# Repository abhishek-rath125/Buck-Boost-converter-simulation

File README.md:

# Single-Stage Buck / Boost Demonstrator (555-timer PWM & KiCad PCB)

**Author:** Abhishek Rathour — B.Tech, Electrical & Electronics Engineering, NIT Goa

A complete power electronics project demonstrating **buck-mode (step-down) and boost-mode (step-up) behaviour from a single power-stage topology**, featuring both **LTspice simulation suites** and a physical **KiCad 10 hardware design & 2-layer PCB layout**.

---

## 📸 Hardware Previews

| Assembled 3D Board Render | KiCad 2-Layer PCB Layout |
|:---:|:---:|
|  |  |
| *3D view showing electrolytic cap bank, TO-220 MOSFET heatsink, NE555P, trimmer pot & inductors* | *2-layer routed board (`buckboostv1.kicad_pcb`)* |

### KiCad Schematic Diagram

*Complete hardware schematic (`hardware/buckboostv1.kicad_sch`) with NE555P astable PWM generator, potentiometer duty-cycle steering, and dual-inductor SEPIC power stage.*

---

## ⚡ What this is

A unified simulation and hardware project demonstrating how a single power stage behaves as either a **buck converter** (output below $V_{in}$) or a **boost converter** (output above $V_{in}$), purely by controlling the PWM switch duty cycle:

- **Duty cycle $D < 50\%$** $\longrightarrow$ Buck mode (step-down magnitude).
- **Duty cycle $D > 50\%$** $\longrightarrow$ Boost mode (step-up magnitude).

The repository documents the complete engineering trail:
1. **LTspice Simulation Trail:** Diagnosing inverting-topology issues, migrating to a two-inductor SEPIC stage, solving ripple current via switching frequency vs. duty-cycle moderation, and isolating the 555 supply rail.
2. **KiCad Hardware Implementation (`buckboostv1`):** Translating the simulation into a physical, manufacture-ready 2-layer PCB with a single potentiometer (`RV1`) for continuous, real-time duty cycle tuning on the lab bench.

---

## 🗂️ Repo Structure

```
├── hardware/
│   ├── buckboostv1.kicad_pro        # KiCad 10 project definition
│   ├── buckboostv1.kicad_sch        # Hardware schematic
│   ├── buckboostv1.kicad_pcb        # 2-layer routed PCB layout
│   ├── schematic.pdf                # High-res vector PDF export
│   ├── buckboostv1.svg              # Scalable vector graphics export
│   ├── bom.csv                      # Full Bill of Materials
│   ├── README.md                    # Hardware & PCB fabrication guide
│   └── gerbers/                     # Production Gerbers & NC drill files (JLCPCB/PCBWay)
├── ltspice/
│   ├── v1_sepic_fast_switching/     # Two-inductor power stage, 131 kHz switching
│   ├── draft1_555_vcc_isolation_test/ # Standalone 12V 555 testbench
│   └── v3_final/                    # Converter with dedicated 12V rail, 13.1 kHz
├── docs/
│   ├── 01-topology-and-goal.md      # Dual-mode operation & diode-steered 555 astable
│   ├── 02-v1-sepic-fast-switching.md
│   ├── 03-draft1-vcc-isolation-test.md
│   ├── 04-v3-final-fixes.md
│   ├── 05-hardware-kicad-pcb.md     # Detailed hardware & PCB design notes
│   ├── hardware/                    # Board renders and layout screenshots
│   └── v3_simulation_result.png     # LTspice waveform verification
├── CHANGELOG.md                     # Revision history
├── LICENSE                          # MIT License
└── README.md
```

---

## 🛠️ Hardware & PCB Design Details

### Continuous Duty Cycle Tuning via Potentiometer `RV1`
In physical hardware, fixed resistors are replaced by a **10kΩ vertical trimmer potentiometer (`RV1`)** coupled with antiparallel steering diodes `D1` and `D2`:
- Turning `RV1` clockwise increases charging resistance $\rightarrow$ **Duty cycle $D > 50\%$ (Boost)**.
- Turning `RV1` counter-clockwise increases discharge resistance $\rightarrow$ **Duty cycle $D < 50\%$ (Buck)**.
- A single knob controls real-time continuous transitions from step-down to step-up.

### Key Hardware Components
| Reference | Part | Package | Role |
|---|---|---|---|
| **U1** | NE555P | DIP-8 | High-precision PWM astable oscillator |
| **Q1** | IRF3205 | TO-220 / TO-218 | 55V, 110A, 8mΩ N-Channel power MOSFET |
| **RV1** | Potentiometer | ACP CA9-V10 | Real-time duty-cycle adjustment |
| **D1, D2** | 1N4148 / DO-35 | Axial | Independent charge/discharge steering diodes |
| **D3** | BAT54C / Schottky | TO-126-3 | Ultra-fast freewheeling diode |
| **L2, L3** | Power Chokes | Fastron MECC Axial | Energy storage dual inductors |
| **C2-C5** | Radial Electrolytic | D10mm, P5mm | Low-ESR AC coupling, filter & timing caps |
| **J1** | 2-Pin Terminal | JWT A3963 | DC power input connector |

Fabrication Gerbers and drill files are located in [`hardware/gerbers/`](hardware/gerbers/). See [`hardware/README.md`](hardware/README.md) for manufacturing guidelines.

---

## 📊 Simulation Summary (LTspice)

| Parameter | v1 | Draft1 | v3 (Final) |
|---|---|---|---|
| **Power stage** | SEPIC-style, 2 inductors | *(none — timer only)* | SEPIC-style, 2 inductors |
| **Switching frequency** | 1nF $\rightarrow$ **~131 kHz** | 10nF $\rightarrow$ ~9.3 kHz | 10nF $\rightarrow$ **~13.1 kHz** |
| **Duty cycle (2 channels)** | 27.3% / **81.8%** | 29.5% (single channel) | **39.1% / 63.6%** |
| **Inductor ripple current** | ~0.5 A / ~1.5 A | n/a | ~0.7 A / ~1.2 A |
| **555 Vcc** | Shared 24V rail ⚠️ | **Dedicated 12V** ✅ | **Dedicated 12V** ✅ |
| **Coupling-cap damping** | none | n/a | 22 Ω (`R11`/`R12`) |
| **Output-cap ESR** | none | n/a | modeled (`Rser = 0.1Ω`) |

### Verification Waveforms (v3)

With input $V_{ref} = 24\,\text{V}$:
- **Buck Channel (`U1`, $D = 39.1\%$):** Output settles at **$13.50\,\text{V}$** (step-down confirmed).
- **Boost Channel (`U2`, $D = 63.6\%$):** Output settles at **$29.43\,\text{V}$** (step-up confirmed).

---

## 💻 How to Open the Design Files

- **KiCad Design Files:** Open [`hardware/buckboostv1.kicad_pro`](hardware/buckboostv1.kicad_pro) in **KiCad 10** (or 8 / 9). All footprints, schematic symbols, and 3D models use standard KiCad libraries.
- **LTspice Simulations:** Open any `.asc` file in [`ltspice/`](ltspice/) using free LTspice (Windows, macOS, or Wine on Linux). Built-in generic models are used throughout.

---

## 📜 License

MIT License — see [LICENSE](LICENSE).

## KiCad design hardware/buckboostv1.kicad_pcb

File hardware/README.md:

# Hardware & PCB Implementation (KiCad 10)

This directory contains the complete hardware design, schematic, 2-layer PCB layout, Bill of Materials (BOM), and manufacturing Gerber files for the **Single-Stage Buck / Boost Demonstrator**.

---

## 📐 Circuit Architecture

The hardware translates the dual-mode SEPIC / buck-boost topology into a physical board powered by a single supply and tuned in real time via an on-board trimmer potentiometer:

1. **Continuous Duty-Cycle PWM Generator (NE555P):**
   - Configured as an astable multivibrator with diode steering (`D1`, `D2`).
   - Single trimmer potentiometer (`RV1`) adjusts the ratio between charge resistance and discharge resistance without changing total cycle period drastically.
   - Turning `RV1` allows seamless on-the-fly transition between **Buck mode ($D < 50\%$)** and **Boost mode ($D > 50\%$)**.
   - Output pin 3 drives the gate of power MOSFET `Q1` through gate damping resistor `R2`.

2. **SEPIC Power Stage:**
   - **Switch (`Q1`):** IRF3205 N-Channel MOSFET in a TO-220/TO-218 vertical package mounted with heatsink clearance for thermal dissipation.
   - **Inductors (`L3`, `L2`):** Dual high-current inductors (input choke and output inductor) supporting energy storage in both CCM and DCM modes.
   - **Coupling Capacitor (`C3`):** High-capacitance electrolytic block blocking DC while passing switching ripple.
   - **Freewheeling Diode (`D3`):** Fast switching Schottky diode (`BAT54C` / TO-126 package) for low forward drop and minimal reverse recovery losses.
   - **Output Filter (`C4`, `R4`):** Low-ESR electrolytic capacitor bank with dummy load resistor `R4`.

---

## 📦 Bill of Materials (BOM)

| Reference | Value / Part | Package / Footprint | Description / Purpose |
|---|---|---|---|
| **U1** | NE555P | DIP-8 (`W7.62mm`) | Precision Timer IC (PWM oscillator) |
| **Q1** | IRF3205 | TO-218-3 / TO-220 Vertical | 55V, 110A, 8mΩ N-Channel Power MOSFET |
| **RV1** | R_Potentiometer | ACP CA9-V10 Vertical | Trimmer potentiometer for duty cycle tuning |
| **D1, D2** | Fast Switching Diode | DO-35 (SOD27) / Axial | Steering diodes for independent charge/discharge |
| **D3** | BAT54C / Schottky | TO-126-3 Vertical | High-speed freewheeling rectifier |
| **L2, L3** | Inductors (Power Chokes) | Axial Fastron MECC (`P7.62mm`) | Dual energy storage inductors |
| **C2** | Filter Cap | Radial D10mm, P5.0mm | 555 Pin 5 (CONT) noise decoupling |
| **C3** | Coupling Cap | Radial D10mm, P5.0mm | AC energy transfer capacitor |
| **C4** | Output Cap | Radial D10mm, P5.0mm | DC output voltage smoothing filter |
| **C5** | Timing Cap | Radial D10mm, P5.0mm | 555 astable timing capacitor |
| **R1** | Pull-up Resistor | Axial DIN0204 (`P5.08mm`) | Discharge pullup from Vcc to Pin 7 |
| **R2** | Gate Resistor | Axial DIN0204 (`P5.08mm`) | MOSFET gate damping resistor (suppresses ringing) |
| **R3** | Damping Resistor | Axial DIN0204 (`P5.08mm`) | Coupling-loop damping resistor |
| **R4** | Load Resistor | Axial DIN0204 (`P5.08mm`) | Output test load |
| **J1** | Conn_01x02_Pin | JWT A3963 2-pin (`P3.96mm`) | DC power input connector |

---

## 🗂️ File Directory

- [`buckboostv1.kicad_pro`](buckboostv1.kicad_pro) — KiCad 10 project definition file.
- [`buckboostv1.kicad_sch`](buckboostv1.kicad_sch) — Complete hierarchical schematic with netlabels and title block.
- [`buckboostv1.kicad_pcb`](buckboostv1.kicad_pcb) — 2-layer routed PCB layout with power planes.
- [`schematic.pdf`](schematic.pdf) — High-resolution vector PDF export of the schematic.
- [`buckboostv1.svg`](buckboostv1.svg) — Scalable vector graphics export of the schematic.
- [`bom.csv`](bom.csv) — Comma-separated Bill of Materials export.
- [`gerbers/`](gerbers/) — Production-ready Gerber and Excellon drill files.

---

## 🏭 PCB Fabrication Details

The files in [`gerbers/`](gerbers/) are directly compatible with standard PCB fabricators (JLCPCB, PCBWay, OSH Park):

| Extension | Layer Description | Fabricator Layer Name |
|---|---|---|
| `.gtl` | Front / Top Copper | Top Layer |
| `.gbl` | Back / Bottom Copper | Bottom Layer |
| `.gts` | Front / Top Solder Mask | Top Solder Mask |
| `.gbs` | Back / Bottom Solder Mask | Bottom Solder Mask |
| `.gto` | Front / Top Silkscreen | Top Overlay / Silkscreen |
| `.gbo` | Back / Bottom Silkscreen | Bottom Overlay / Silkscreen |
| `.gm1` | Board Outline / Edge Cuts | Mechanical 1 / Edge Cuts |
| `.drl` | Excellon NC Drill File | Plated / Non-Plated Through Holes |

### Recommended Fab Specifications:
- **Board Thickness:** 1.6 mm
- **Copper Weight:** 1 oz (35 µm) or 2 oz (for high current demonstrator runs)
- **Minimum Trace Width / Spacing:** 0.25 mm / 0.25 mm
- **Surface Finish:** HASL (with lead) or ENIG
- **Solder Mask Color:** Green / Matte Black

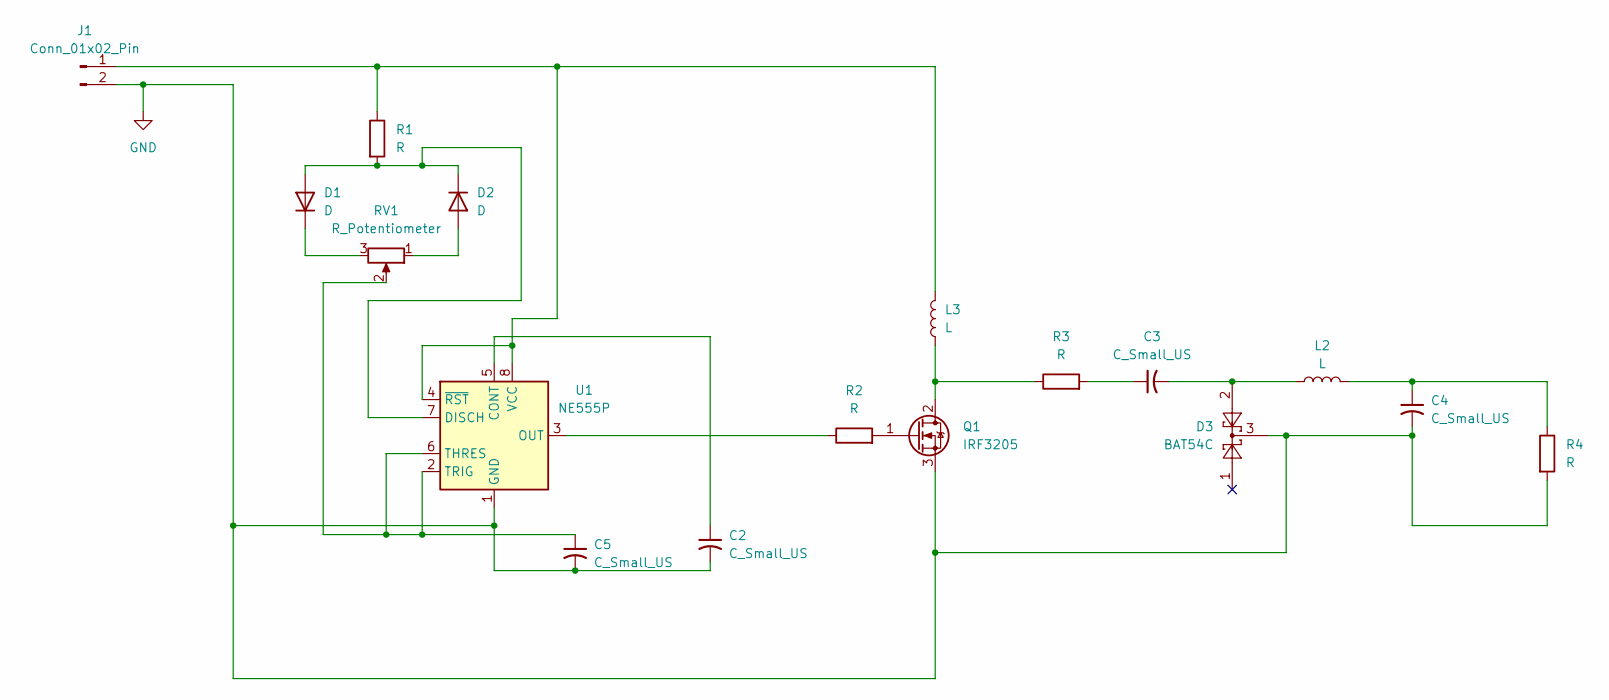
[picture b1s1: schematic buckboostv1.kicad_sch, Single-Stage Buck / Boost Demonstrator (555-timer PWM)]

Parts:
C2, C3, C4, C5: C_Small_US; CP_Radial_D10.0mm_P5.00mm
D1: D; D_DO-35_SOD27_P7.62mm_Horizontal
D2: D
D3: BAT54C; TO-126-3_Vertical
J1: Conn_01x02_Pin; JWT_A3963_1x02_P3.96mm_Vertical
L2, L3: L; L_Axial_L11.0mm_D4.5mm_P7.62mm_Vertical_Fastron_MECC
Q1: IRF3205; TO-218-3_Vertical
R1, R2, R3, R4: R; R_Axial_DIN0204_L3.6mm_D1.6mm_P5.08mm_Horizontal
RV1: R_Potentiometer; Potentiometer_ACP_CA9-V10_Vertical
U1: NE555P; DIP-8_W7.62mm

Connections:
GND: C2.2, C4.2, C5.2, D3.3, J1.2, Q1.3 (S), R4.2, U1.1 (GND)
unnamed: C3.1, R3.2
unnamed: C3.2, D3.2, L2.1
unnamed: C4.1, L2.2, R4.1
unnamed: D1.2 (A), D2.1 (K), R1.2, U1.7 (DISCH)
unnamed: D1.1 (K), RV1.3
unnamed: D2.2 (A), RV1.1
unnamed: J1.1, L3.2, R1.1, U1.4 (~RST), U1.8 (VCC)
unnamed: L3.1, Q1.2 (D), R3.1
unnamed: Q1.1 (G), R2.2
unnamed: C2.1, U1.5 (CONT)
unnamed: R2.1, U1.3 (OUT)
unnamed: C5.1, RV1.2, U1.2 (TRIG), U1.6 (THRES)

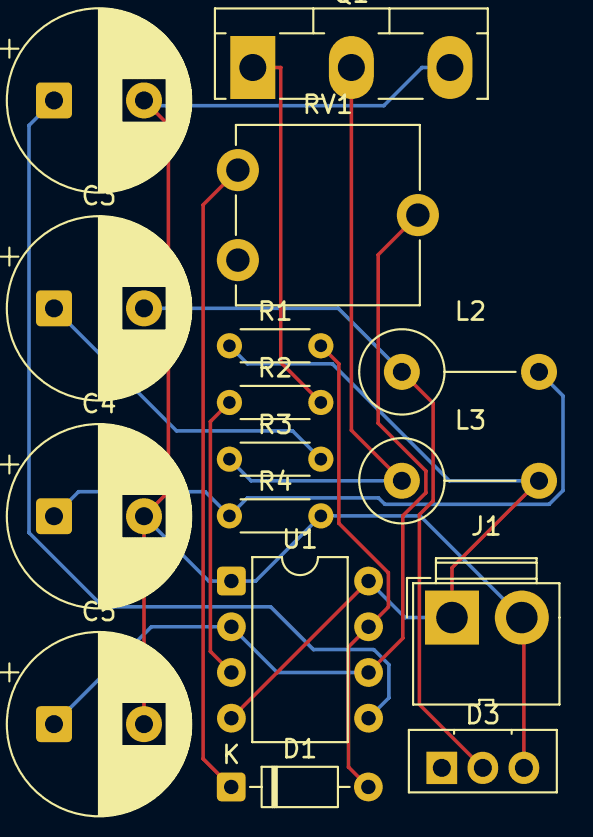
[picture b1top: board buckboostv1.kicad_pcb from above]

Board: 2 copper layers, 16 parts (0 on the bottom side), 12 nets.
